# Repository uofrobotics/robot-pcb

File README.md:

# Robot PCB

## Front PCB

## Back PCB

## Front Copper Layer

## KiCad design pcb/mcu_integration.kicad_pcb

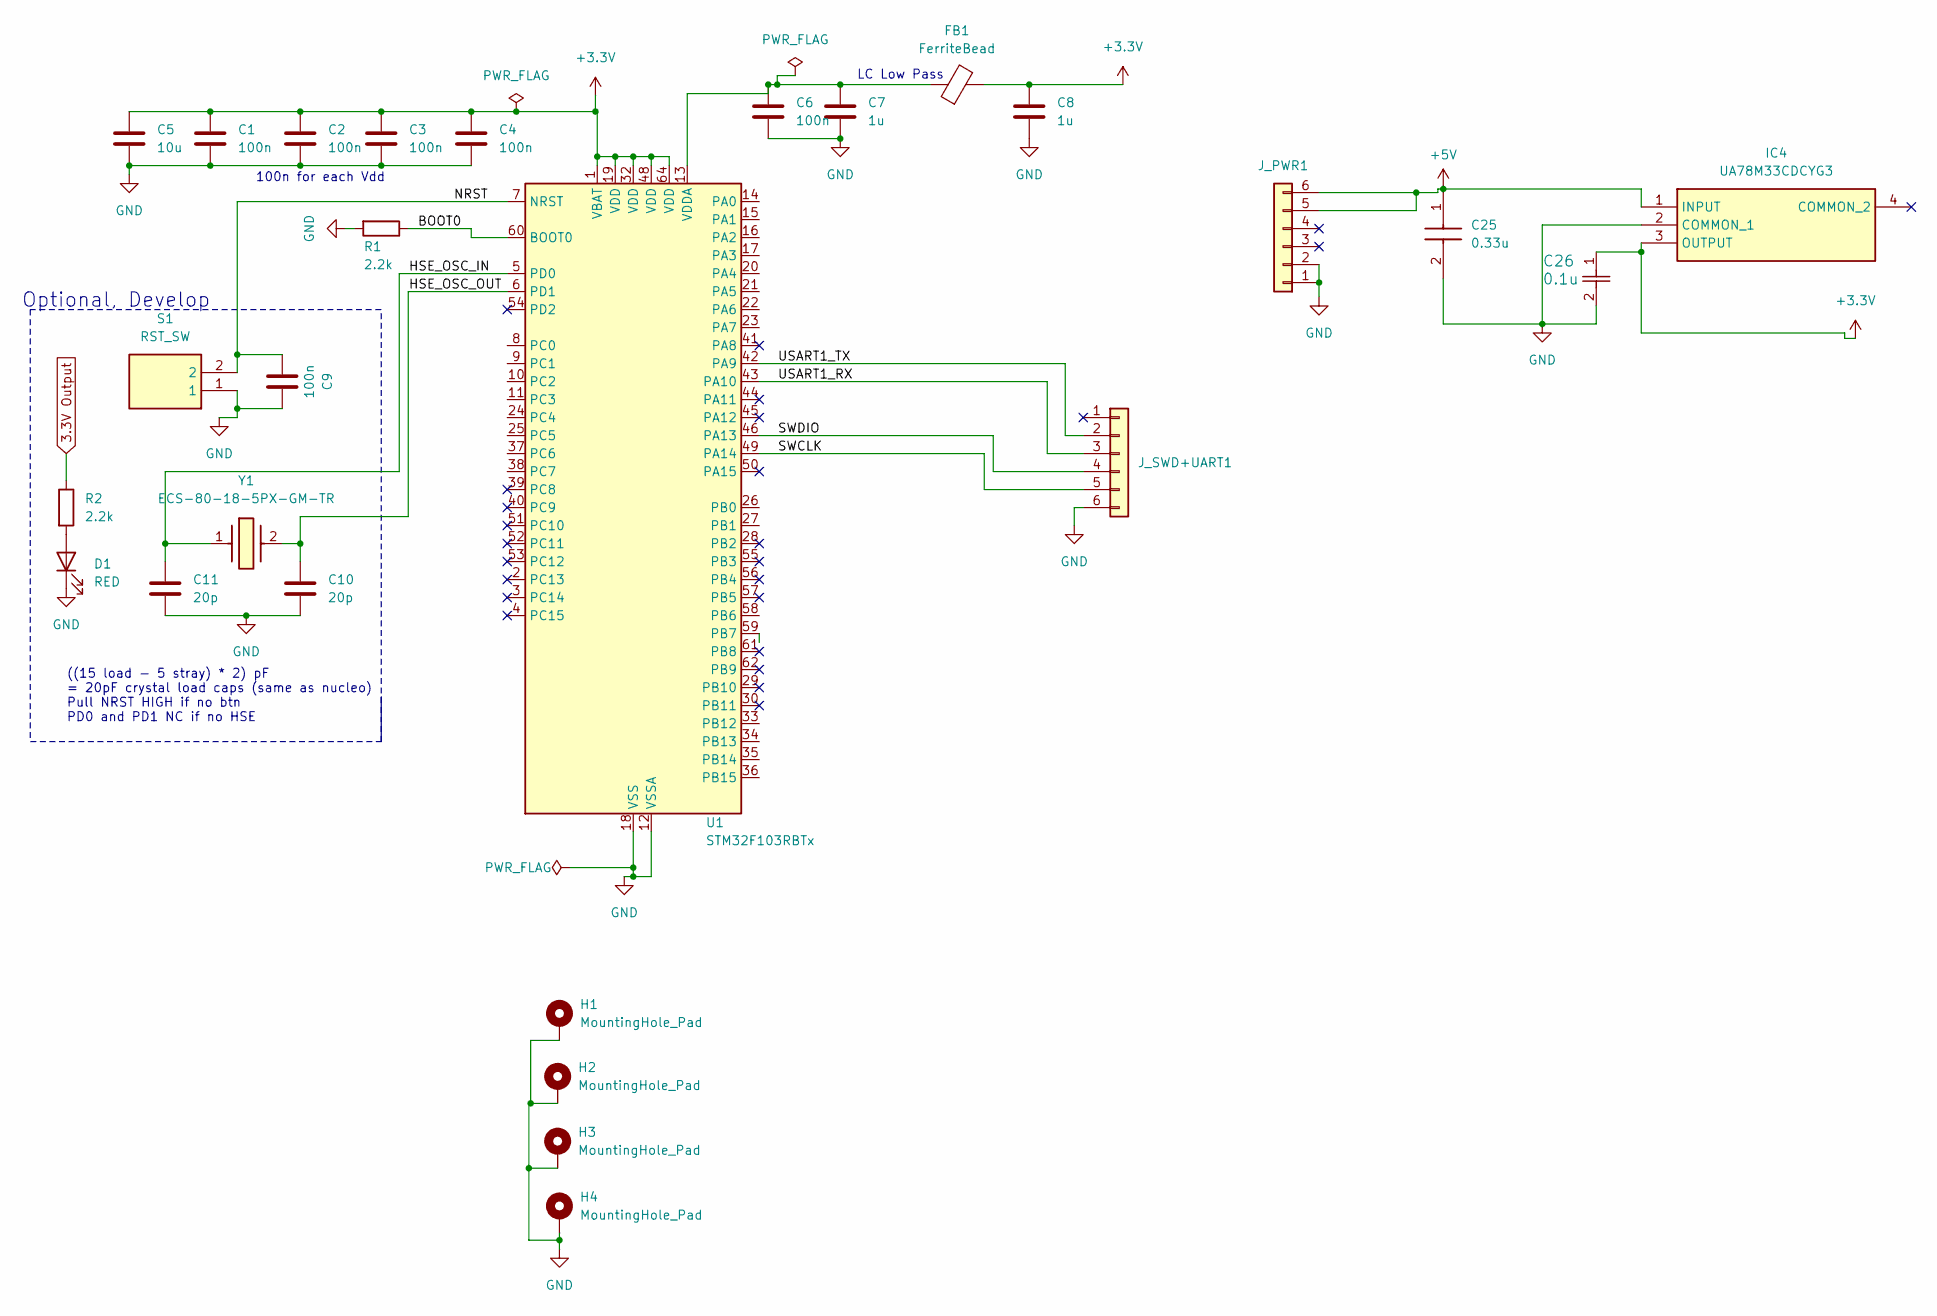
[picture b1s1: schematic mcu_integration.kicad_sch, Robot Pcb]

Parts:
C1: 100n; R_0402_1005Metric
C2, C3, C4, C6, C9: 100n; C_0402_1005Metric
C5: 10u; C_0603_1608Metric
C7, C8: 1u; C_0402_1005Metric
C10, C11: 20p; C_0402_1005Metric
C25: 0.33u; C0805; Mouser Part Number 80-C0805C334K3RAULR
C26: 0.1u; CAPC220145_88N_KEM-0.1u
D1: RED; LED_0603_1608Metric
FB1: FerriteBead; L_0603_1608Metric
H1, H2, H3, H4: MountingHole_Pad; MountingHole_3.2mm_M3_Pad_Via
IC4: UA78M33CDCYG3; SOT230P700X180-4N; Mouser Part Number 595-UA78M33CDCYG3
J_PWR1: Conn_01x06; PinHeader_1x06_P2.54mm_Vertical
J_SWD+UART1: Conn_01x06; PinHeader_1x06_P2.54mm_Vertical
R1, R2: 2.2k; R_0402_1005Metric
S1: RST_SW; 95C04A3GWRT; Mouser Part Number 706-95C04A3GWRT
U1: STM32F103RBTx; LQFP-64_10x10mm_P0.5mm
Y1: ECS-80-18-5PX-GM-TR; ECS80185PXGMTR; Mouser Part Number 520-80-18-5PX-GM-TR

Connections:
3.3V Output: R2.1
+3.3V: C1.1, C2.1, C3.1, C4.1, C5.1, C8.1, C26.1, FB1.2, IC4.3 (OUTPUT), U1.1 (VBAT), U1.19 (VDD), U1.32 (VDD), U1.48 (VDD), U1.64 (VDD)
+5V: C25.1, IC4.1 (INPUT), J_PWR1.5, J_PWR1.6
/BOOT0: R1.1, U1.60 (BOOT0)
/HSE_OSC_IN: C11.1, U1.5 (PD0), Y1.1
/HSE_OSC_OUT: C10.1, U1.6 (PD1), Y1.2
/NRST: C9.2, S1.2, U1.7 (NRST)
/SWCLK: J_SWD+UART1.5, U1.49 (PA14)
/SWDIO: J_SWD+UART1.4, U1.46 (PA13)
/USART1_RX: J_SWD+UART1.3, U1.43 (PA10)
/USART1_TX: J_SWD+UART1.2, U1.42 (PA9)
GND: C1.2, C2.2, C3.2, C4.2, C5.2, C6.2, C7.2, C8.2, C9.1, C10.2, C11.2, C25.2, C26.2, D1.1 (K), H1.1, H2.1, H3.1, H4.1, IC4.2 (COMMON_1), J_PWR1.1, J_PWR1.2, J_SWD+UART1.6, R1.2, S1.1, U1.12 (VSSA), U1.18 (VSS), U1.31 (VSS), U1.47 (VSS), U1.63 (VSS)
unnamed: D1.2 (A), R2.2
unnamed: C6.1, C7.1, FB1.1, U1.13 (VDDA)

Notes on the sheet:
((15 load - 5 stray) * 2) pF = 20pF crystal load caps (same as nucleo) Pull NRST HIGH if no btn PD0 and PD1 NC if no HSE
Optional, Develop
100n for each Vdd
LC Low Pass

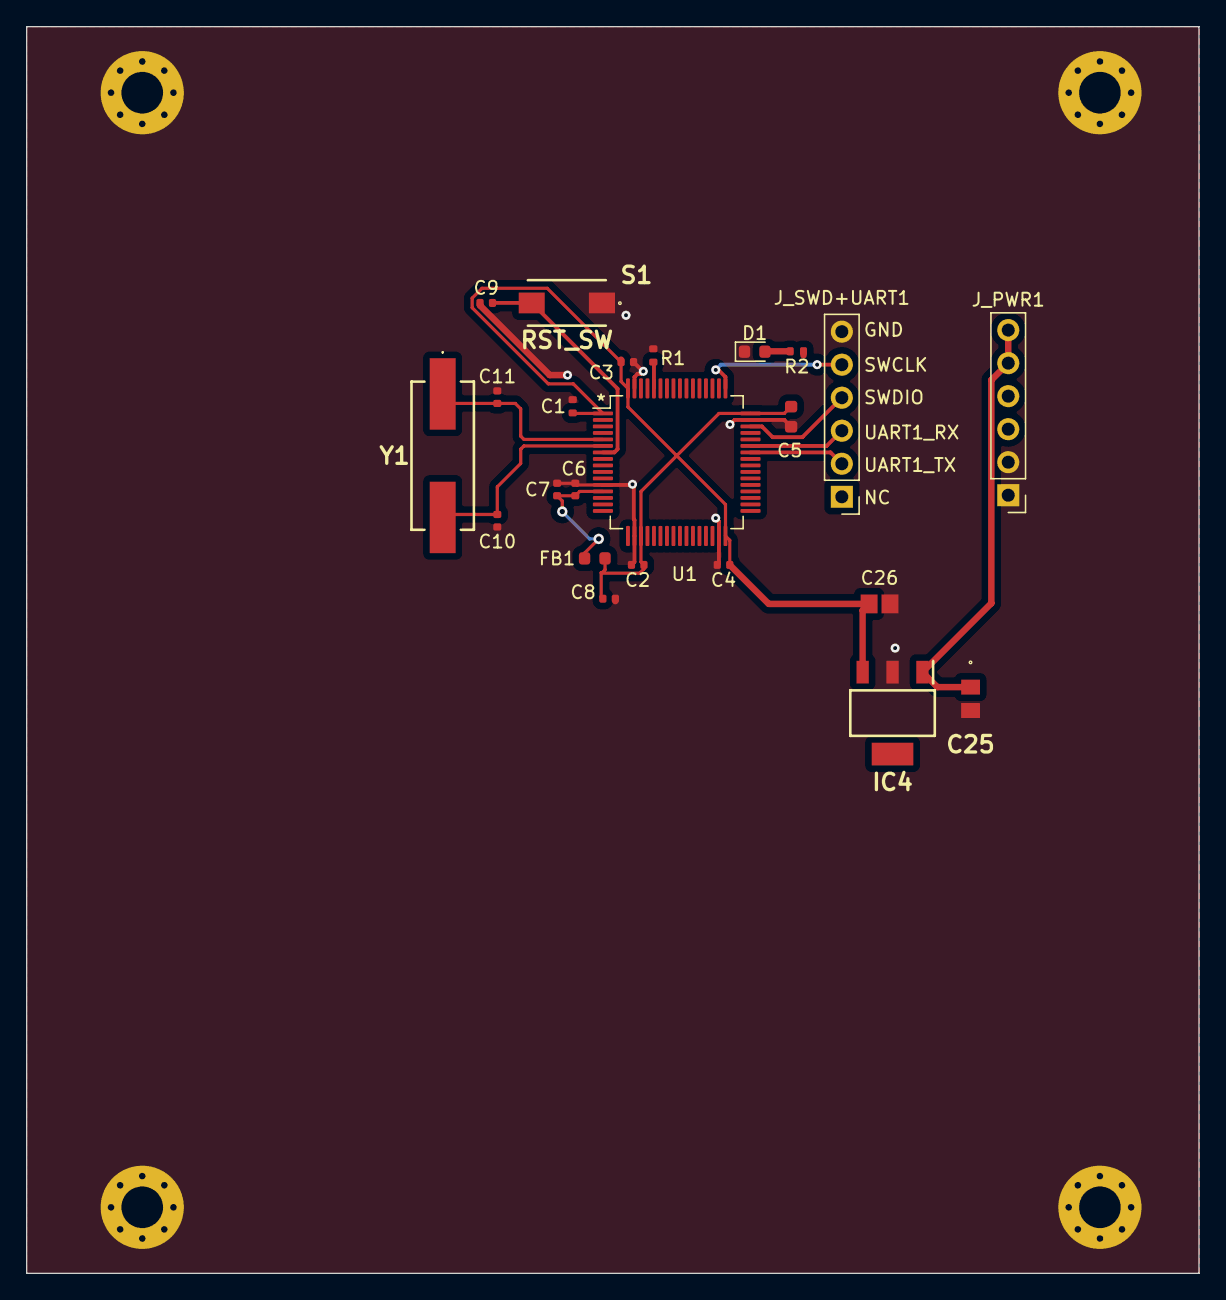
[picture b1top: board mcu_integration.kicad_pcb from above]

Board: 4 copper layers, 90.2 x 95.9 mm, 27 parts (0 on the bottom side), 13 nets.

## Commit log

2024-03-13 bare mcu implementation
2024-03-13 add front pcb picture to readme
